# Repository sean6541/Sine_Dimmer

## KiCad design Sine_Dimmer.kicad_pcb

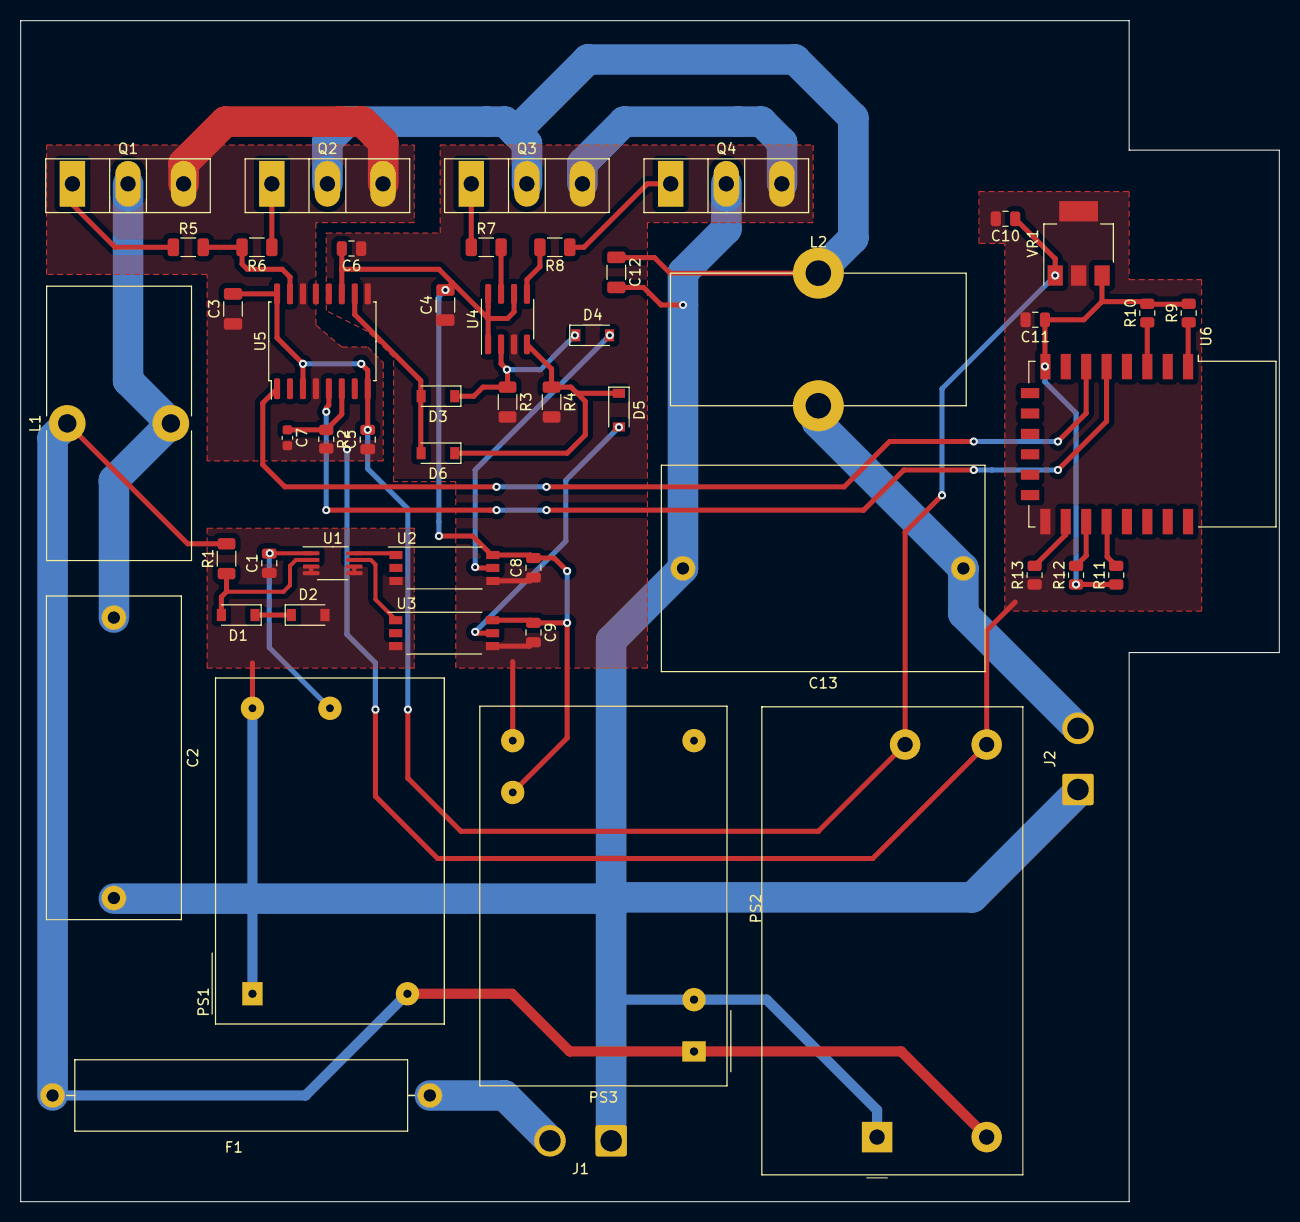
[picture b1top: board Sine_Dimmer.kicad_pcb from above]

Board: 2 copper layers, 123.4 x 115.8 mm, 51 parts (0 on the bottom side), 36 nets.

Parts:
C1, C5, C6, C8, C9, C10, C11: 1u; C_0805_2012Metric
C2: 4.7u; C_Rect_L31.5mm_W13.0mm_P27.50mm_MKS4
C3, C4: 2.2u; C_1206_3216Metric
C7: 0.1u; C_0603_1608Metric
C12: 2.2n; C_1206_3216Metric
C13: 10u; C_Rect_L31.5mm_W20.0mm_P27.50mm_MKS4
D1, D2: 3; D_SOD-123
D3, D4, D5, D6: D; D_SOD-123
F1: 15; Fuse_SunFuse-6HP
J1: Input; SolderWire-1.5sqmm_1x02_P6mm_D1.7mm_OD3mm
J2: Output; SolderWire-1.5sqmm_1x02_P6mm_D1.7mm_OD3mm
L1: 47u; L_Toroid_Vertical_L26.7mm_W14.0mm_P10.16mm_Pulse_D
L2: 100u; uxcell_Toroid_100uH_20A
PS1: IRM-02-5; Converter_ACDC_MeanWell_IRM-02-xx_THT
PS2: IRM-05-12; Converter_ACDC_MeanWell_IRM-05-xx_THT
PS3: IRM-03-12; Converter_ACDC_MeanWell_IRM-03-xx_THT
Q1, Q2, Q3, Q4: IPW60R037P7; TO-247-3_Vertical
R1: 100k; R_1206_3216Metric
R2: 5.1k; R_0805_2012Metric
R3, R4: 1k; R_1206_3216Metric
R5, R6, R7, R8: 0; R_1206_3216Metric
R9, R10, R11, R12, R13: 3.3k; R_0805_2012Metric
U1: LT1711; MSOP-8_3x3mm_P0.65mm
U2, U3: TLP2745; SO-6L_10x3.84mm_P1.27mm
U4: 2EDN7424F; SOIC-8_3.9x4.9mm_P1.27mm
U5: UCC20520; SOIC-16W_7.5x10.3mm_P1.27mm
U6: ESP-12E
VR1: UA78M33CDCYR; SOT-223

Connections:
GND: C3.1, C5.1, C7.2, C10.2, C11.2, PS2.3, Q1.3, Q2.3, R2.2, R13.1, U5.4, U5.14, U6.15, VR1.2, VR1.4
LINE: F1.1, L1.1, PS1.2, PS2.2, PS3.1, R1.2
NEUT: C1.1, C2.2, C12.2, C13.2, D2.2, J1.1, J2.1, PS1.1, PS1.3, PS2.1, PS3.3, Q4.2, U1.3, U1.4, U1.5, U1.6, U2.3, U3.3
unnamed: C1.2, PS1.4, U1.1
unnamed: C2.1, L1.2, Q1.2
unnamed: C7.1, R2.1, U5.6
unnamed: C11.1, R9.2, R10.2, R11.1, R12.1, U6.8, VR1.3
unnamed: C12.1, L2.1, Q2.2, Q3.2
unnamed: D1.1, D2.1
unnamed: D1.2, R1.1, U1.2
unnamed: D3.1, D4.1, R3.1, U4.2
unnamed: D3.2, D6.2, U5.10
unnamed: D5.1, D6.1, R4.1, U4.4
unnamed: F1.2, J1.2
unnamed: Q1.1, R5.1
unnamed: Q2.1, R6.1
unnamed: Q3.1, R7.1
unnamed: Q4.1, R8.1
unnamed: R5.2, R6.2, U5.15
unnamed: R7.2, U4.7
unnamed: R8.2, U4.5
unnamed: R9.1, U6.1
unnamed: R10.1, U6.3
unnamed: R11.2, U6.18
unnamed: R12.2, U6.17
unnamed: R13.2, U6.16
unnamed: U1.7, U3.1
unnamed: U1.8, U2.1
VCC: C3.2, C5.2, C10.1, PS2.4, U5.3, U5.8, U5.16, VR1.1
VDD: C4.2, C6.2, C8.2, C9.1, PS3.16, U2.6, U3.6, U4.1, U4.6, U4.8, U5.11
VPP: C13.1, J2.2, L2.2
VSS: C4.1, C6.1, C8.1, C9.2, PS3.14, Q3.3, Q4.3, R3.2, R4.2, U2.4, U3.4, U4.3, U5.9
dis: U5.5, U6.5
fwd: D5.2, U3.5
pwm: U5.1, U6.6
rev: D4.2, U2.5

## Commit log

2020-12-22 Initial Release
2020-12-23 Add JLCPCB
